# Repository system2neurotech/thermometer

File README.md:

# thermometer
Easy to make thermometer using available parts that don't require calibration. 

Building the Firmware 

Use STM32CubeIDE (https://www.st.com/en/development-tools/stm32cubeide.html)

For LCD use the  LCD brance, for LED use the LED branch. You can construct the hardware with either LCD support or LED support, but not both!

The PCB design has been modified since the incarnation I used for testing. Please check it before manufacturing it.

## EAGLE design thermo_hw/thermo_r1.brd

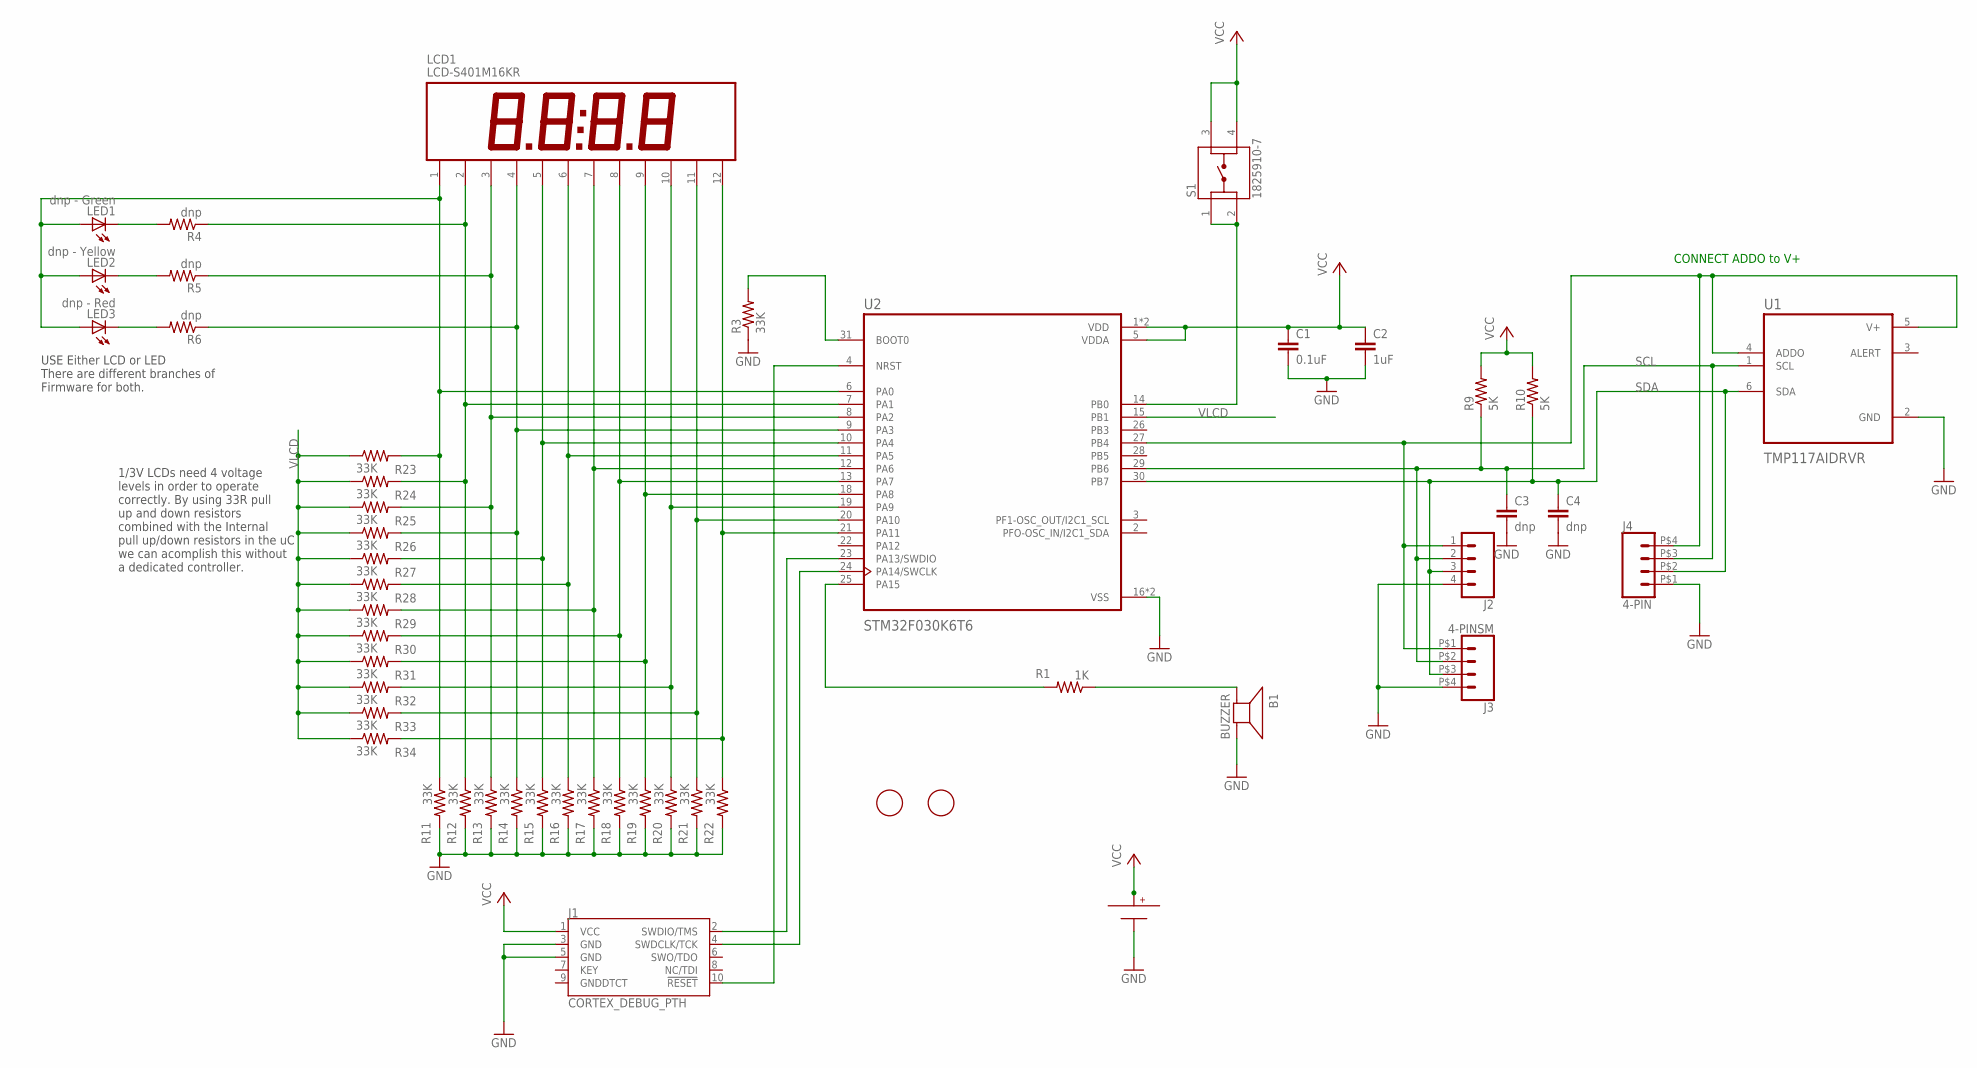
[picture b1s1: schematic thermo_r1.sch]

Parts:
B1: BUZZER; PLKCS1212E
BT1: BAT-HLD-001
C1: 0.1uF; R0603
C2: 1uF; R0603
C3, C4: dnp; R0603
J1: CORTEX_DEBUG_PTH; 2X5-PTH-1.27MM
J2: CONN_041.27MM; 1X04_1.27MM
J3: 4-PINSM; 4PIN_1MM
J4: 4-PIN; 2X2PIN_1MM
LCD1: LCD-S401M16KR
LED1: dnp - Green; CHIP-LED0805
LED2: dnp - Yellow; CHIP-LED0805
LED3: dnp - Red; CHIP-LED0805
R1: 1K; R0603
R3, R11, R12, R13, R14, R15, R16, R17, R18, R19, R20, R21, R22, R23, R24, R25, R26, R27, R28, R29, R30, R31, R32, R33, R34: 33K; R0603
R4, R5, R6: dnp; R0603
R9, R10: 5K; R0603
S1: 1825910-7; SW_1825910-7
U1: TMP117AIDRVR; SON65P200X200X80-7N
U2: STM32F030K6T6; QFP80P900X900X160-32N
U$5, U$6: FIDUCIAL; FIDUCIAL_1MM

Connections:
GND: B1.P$2 (-), BT1.-, C1.2, C2.2, C3.2, C4.2, J1.3 (GND), J1.5 (GND), J2.4, J3.P$4 (4), J4.P$1 (1), R3.1, R11.2, R12.2, R13.2, R14.2, R15.2, R16.2, R17.2, R18.2, R19.2, R20.2, R21.2, R22.2, U1.2 (GND), U2.16 (VSS), U2.32 (VSS)
unnamed: J1.4 (SWDCLK/TCK), U2.24 (PA14/SWCLK)
unnamed: LCD1.2, R4.1, R12.1, R24.2, U2.7 (PA1)
unnamed: LCD1.3, R5.1, R13.1, R25.2, U2.8 (PA2)
unnamed: LCD1.4, R6.1, R14.1, R26.2, U2.9 (PA3)
unnamed: LCD1.5, R15.1, R27.2, U2.10 (PA4)
unnamed: LCD1.6, R16.1, R28.2, U2.11 (PA5)
unnamed: LCD1.7, R17.1, R29.2, U2.12 (PA6)
unnamed: LCD1.8, R18.1, R30.2, U2.13 (PA7)
unnamed: LCD1.9, R19.1, R31.2, U2.18 (PA8)
unnamed: LCD1.10, R20.1, R32.2, U2.19 (PA9)
unnamed: LCD1.11, R21.1, R33.2, U2.20 (PA10)
unnamed: LCD1.12, R22.1, R34.2, U2.21 (PA11)
unnamed: R1.2, U2.25 (PA15)
unnamed: R3.2, U2.31 (BOOT0)
unnamed: J1.10 (!RESET), U2.4 (NRST)
unnamed: J1.2 (SWDIO/TMS), U2.23 (PA13/SWDIO)
unnamed: B1.P$1 (+), R1.1
unnamed: LED3.C, R6.2
unnamed: S1.1, S1.2, U2.14 (PB0)
unnamed: LED2.C, R5.2
unnamed: LED1.C, R4.2
unnamed: LCD1.1, LED1.A, LED2.A, LED3.A, R11.1, R23.2, U2.6 (PA0)
SCL: C3.1, J2.2, J3.P$2 (2), J4.P$3 (3), R9.1, U1.1 (SCL), U2.29 (PB6)
SDA: C4.1, J2.3, J3.P$3 (3), J4.P$2 (2), R10.1, U1.6 (SDA), U2.30 (PB7)
VCC: BT1.+@1 (+), BT1.+@2 (+), C1.1, C2.1, J1.1 (VCC), R9.2, R10.2, S1.3, S1.4, U2.1 (VDD), U2.5 (VDDA), U2.17 (VDD)
VLCD: R23.1, R24.1, R25.1, R26.1, R27.1, R28.1, R29.1, R30.1, R31.1, R32.1, R33.1, R34.1, U2.15 (PB1)
VT: J2.1, J3.P$1 (1), J4.P$4 (4), U1.4 (ADDO), U1.5 (V+), U2.27 (PB4)

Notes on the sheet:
CONNECT ADDO to V+
USE Either LCD or LED There are different branches of Firmware for both.
1/3V LCDs need 4 voltage levels in order to operate correctly. By using 33R pull up and down resistors combined with the Internal pull up/down resistors in the uC we can acomplish this without a dedicated controller.

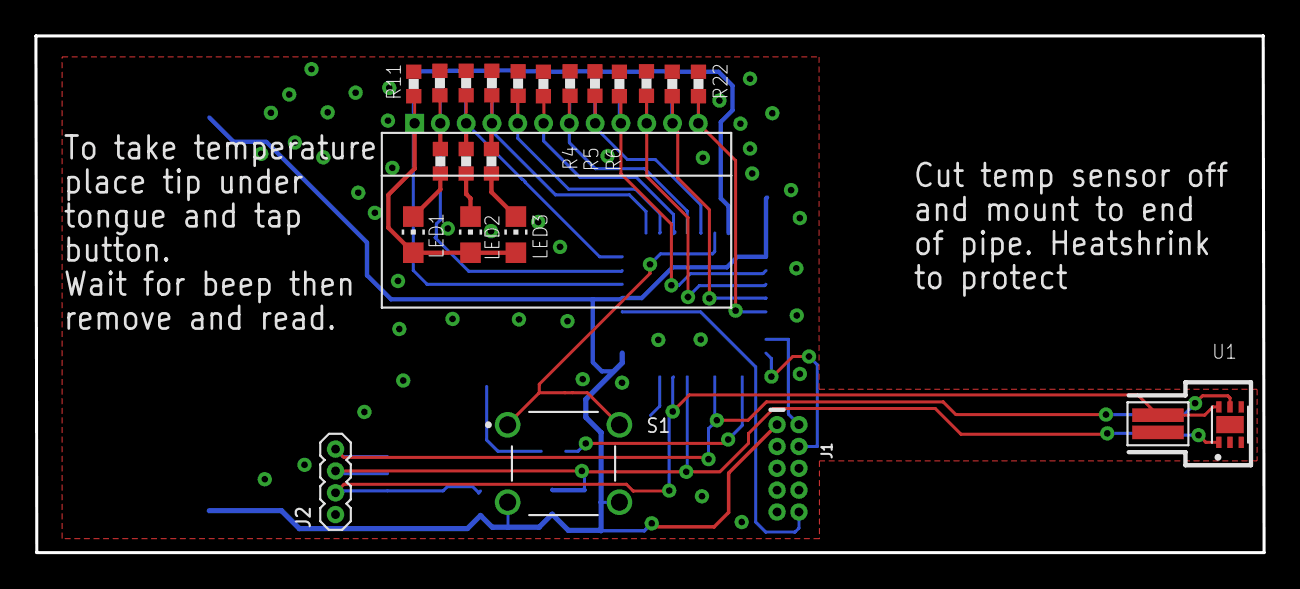
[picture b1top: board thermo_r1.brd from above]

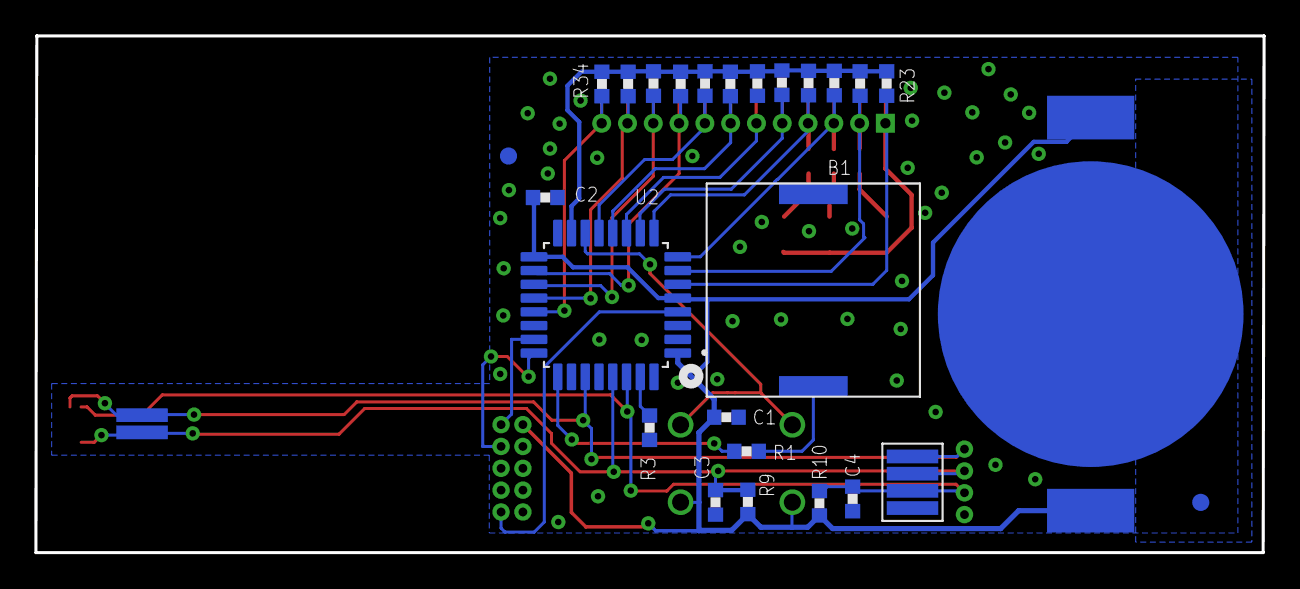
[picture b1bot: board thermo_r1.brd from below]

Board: 2 copper layers, 71.4 x 30.0 mm, 50 parts (26 on the bottom side), 28 nets.

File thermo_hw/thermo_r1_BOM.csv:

Qty,Value,Device,Package,Parts,Description
1,,CONN_041.27MM,1X04_1.27MM,J2,Multi connection point. Often used as Generic Header-pin footprint for 0.1 inch spaced/style header connections
1,0.1uF,CAPACITORC0603,R0603,C1,
1,1825910-7,1825910-7,SW_1825910-7,S1,Switch Tactile OFF (ON) SPST Round Button PC Pins 0.05A 24VDC 100000Cycles 2.55N Thru-Hole Loose
1,1K,RESISTORR0603,R0603,R1,Resistor 0603 1K
2,5K,RESISTORR0603,R0603,"R9,R10",Resistor 0603 5k
1,1uF,CAPACITORC0603,R0603,C2,
1,BAT-HLD-001,BAT-HLD-001,BAT-HLD-001,BT1,Linx Technologies BAT-HLD-001
1,BUZZER,BUZZER,PLKCS1212E,B1,
1,CORTEX_DEBUG_PTH,CORTEX_DEBUG_PTH,2X5-PTH-1.27MM,J1,Cortex Debug Connector - 10 pin
1,LCD-S401M16KR,LCD-S401M16KR,LCD-S401M16KR,LCD1,LUMEX
1,STM32F030K6T6,STM32F030K6T6,QFP80P900X900X160-32N,U2,None
1,TMP117AIDRVR,TMP117AIDRVR,SON65P200X200X80-7N,U1,None
2,dnp,CAPACITORC0603,R0603,"C3, C4",
1,dnp,LEDCHIP-LED0805,CHIP-LED0805,LED1,LED 0805 Green
1,dnp,LEDCHIP-LED0805,LEDCHIP-LED0805,LED2,LED 0805 Yellow
1,dnp,LEDCHIP-LED0805,LEDCHIP-LED0805,LED3,LED 0805 Red
3,dnp,RESISTORR0603,R0603,"R4, R5, R6",
25,33k,RESISTORR0603,R0603,"R3, R11-R34",Resistor 0603 33K

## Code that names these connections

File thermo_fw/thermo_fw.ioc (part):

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Mcu.Name=STM32F031K6Tx
Mcu.Package=LQFP32
Mcu.UserName=STM32F031K6Tx
PA0.GPIOParameters=GPIO_Label
PA0.GPIO_Label=COM0
PA0.Signal=GPIO_Input
PA1.GPIOParameters=GPIO_Label
PA1.GPIO_Label=COM1
PA1.Signal=GPIO_Input
PA10.GPIOParameters=GPIO_Label
PA10.GPIO_Label=LCD7
PA10.Signal=GPIO_Output
PA11.GPIOParameters=GPIO_Label
PA11.GPIO_Label=LCD8
PA11.Signal=GPIO_Output
PA13.GPIOParameters=GPIO_Label
PA13.GPIO_Label=SWDIO
PA13.Mode=Serial_Wire
PA13.Signal=SYS_SWDIO
PA14.GPIOParameters=GPIO_Label
PA14.GPIO_Label=SWCLK
PA14.Mode=Serial_Wire
PA14.Signal=SYS_SWCLK
PA15.GPIOParameters=GPIO_Label
PA15.GPIO_Label=BUZZ
PA15.Signal=S_TIM2_CH1_ETR
PA2.GPIOParameters=GPIO_Label
PA2.GPIO_Label=COM2
PA2.Signal=GPIO_Input
PA3.GPIOParameters=GPIO_Label
PA3.GPIO_Label=COM3
PA3.Signal=GPIO_Input
PA4.GPIOParameters=GPIO_Label
PA4.GPIO_Label=LCD1
PA4.Signal=GPIO_Output
PA5.GPIOParameters=GPIO_Label
PA5.GPIO_Label=LCD2
PA5.Signal=GPIO_Output
PA6.GPIOParameters=GPIO_Label
PA6.GPIO_Label=LCD3
PA6.Signal=GPIO_Output
PA7.GPIOParameters=GPIO_Label
PA7.GPIO_Label=LCD4
PA7.Signal=GPIO_Output
PA8.GPIOParameters=GPIO_Label
PA8.GPIO_Label=LCD5
PA8.Signal=GPIO_Output
PA9.GPIOParameters=GPIO_Label
PA9.GPIO_Label=LCD6
PA9.Signal=GPIO_Output
PB0.GPIOParameters=GPIO_PuPd,GPIO_Label
PB0.GPIO_Label=BUTTON
PB0.GPIO_PuPd=GPIO_PULLUP
PB0.Signal=GPXTI0
PB1.GPIOParameters=GPIO_Label
PB1.GPIO_Label=VLCD
PB1.Signal=GPIO_Output
PB4.GPIOParameters=GPIO_Label
PB4.GPIO_Label=VTEMP
PB4.Signal=GPIO_Output
PB6.Mode=I2C
PB6.Signal=I2C1_SCL
PB7.Mode=I2C
PB7.Signal=I2C1_SDA
PF0-OSC_IN.Mode=HSE-External-Clock-Source
PF0-OSC_IN.Signal=RCC_OSC_IN
RCC.SYSCLKFreq_VALUE=48000000
RCC.SYSCLKSource=RCC_SYSCLKSOURCE_PLLCLK
board=NUCLEO-F031K6
boardIOC=true

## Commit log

2020-04-06 Adding files.
2020-04-06 LCD branch
2020-04-06 updated licence text at top of each file.
2020-04-06 fixed licence data at top of file.
2020-04-06 adding LCD files
2020-04-06 added power control for LCD to match v3 hardware
2020-04-06 removed metadata files that shouldn't be in the repo.
2020-04-06 added assembly pictures

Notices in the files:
parts and their libraries:
SparkFun-Connectors: Licensing: Creative Commons ShareAlike 4.0 International - https://creativecommons.org/licenses/by-sa/4.0
